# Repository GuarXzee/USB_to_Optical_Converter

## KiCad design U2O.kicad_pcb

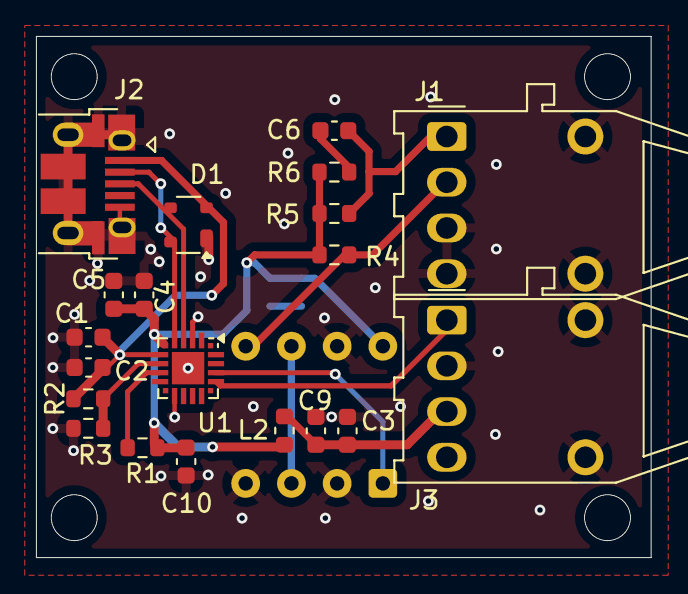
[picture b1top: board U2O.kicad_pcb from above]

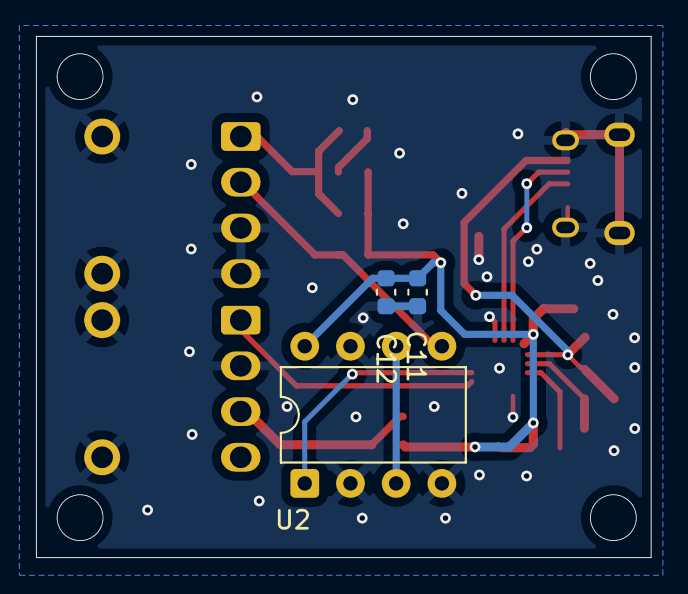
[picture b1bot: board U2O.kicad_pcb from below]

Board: 2 copper layers, 34.1 x 29.0 mm, 23 parts (3 on the bottom side), 14 nets.

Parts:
C1, C3, C4, C11: 100n; C_0603_1608Metric
C2, C5: 4.7u; C_0603_1608Metric
C6: 120p; C_0603_1608Metric
C9, C10, C12: 10u; C_0603_1608Metric
D1: SP0503BAHT; SOT-143
J1: AFBR-1528CZ; Broadcom_AFBR-16xxZ_Horizontal
J2: USB_B_Micro; USB_Micro-B_Amphenol_10103594-0001LF_Horizontal
J3: AFBR-2624Z; Broadcom_AFBR-16xxZ_Horizontal
L2: 1u; L_0603_1608Metric
R1: 10K; R_0603_1608Metric
R2: 22.1K; R_0603_1608Metric
R3: 47.5K; R_0603_1608Metric
R4: 2K; R_0603_1608Metric
R5: 100; R_0603_1608Metric
R6: 15; R_0603_1608Metric
U1: CP2102N-Axx-xQFN20; SiliconLabs_QFN-20-1EP_3x3mm_P0.5mm_EP1.8x1.8mm
U2: SN75454B; DIP-8_W7.62mm

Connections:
D+: D1.3 (K), J2.3 (D+), U1.4 (D+)
D-: D1.4 (K), J2.2 (D-), U1.5 (D-)
GND: C1.2, C2.2, C3.1, C4.2, C5.2, C9.1, C10.1, C11.2, C12.1, D1.1 (A), J1.3 (GND), J1.4 (GND), J1.5 (GND), J1.8 (GND), J2.5 (GND), J2.6 (Shield), J3.2 (VEER), J3.5 (HP), J3.8 (HP), R3.2, U1.3 (GND), U1.12 (GND), U1.21 (GND), U2.2 (1B), U2.4 (GND), U2.7 (2B)
unnamed: C6.2, R6.2
unnamed: C6.1, J1.1 (A), R5.2
unnamed: J1.2 (K), R4.2, U2.5 (2Y)
unnamed: C3.2, C9.2, J3.3 (VCCR), L2.1
unnamed: R1.2, U1.9 (~RST)
unnamed: U2.3 (1Y), U2.6 (2A)
RXD: J3.1 (Data_Out), U1.17 (RXD)
TXD: U1.18 (TXD), U2.1 (1A)
VCC: C4.1, C5.1, C10.2, C11.1, C12.2, L2.2, R1.1, R4.1, R5.1, R6.1, U1.6 (VDD), U2.8 (VCC)
V_DIV: R2.2, R3.1, U1.8 (VBUS)
V_UNREG: C1.1, C2.1, D1.2 (K), J2.1 (VBUS), R2.1, U1.7 (VREGIN)

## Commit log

2025-10-28 First Commit with everything
2025-10-29 one more time
2025-12-13 final push
2025-12-13 With 2 versions
